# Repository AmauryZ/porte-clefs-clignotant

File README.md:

# Porte-clés clignotant 

## Contexte du projet 

Premier circuit imprimé réalisé à l'aide de Kicad consistant à faire clignoter alternativement deux LEDs (verte et bleue).

## Fonctionnement
Le circuit est composé d'un NE555 qui permet de faire clignoter alternativement les deux LEDs. La fréquence du cycle de clignotement est réglable via un potentiomètre.  
Le porte-clés est alimenté par deux piles boutons CR2032.

## Vidéos de démonstration du porte-clés réalisé

https://github.com/user-attachments/assets/a9404657-2942-4910-9b81-8aab252a95bd

https://github.com/user-attachments/assets/f14d513b-74e3-48db-ba6a-31ed8998a323

## Schématique \& PCB

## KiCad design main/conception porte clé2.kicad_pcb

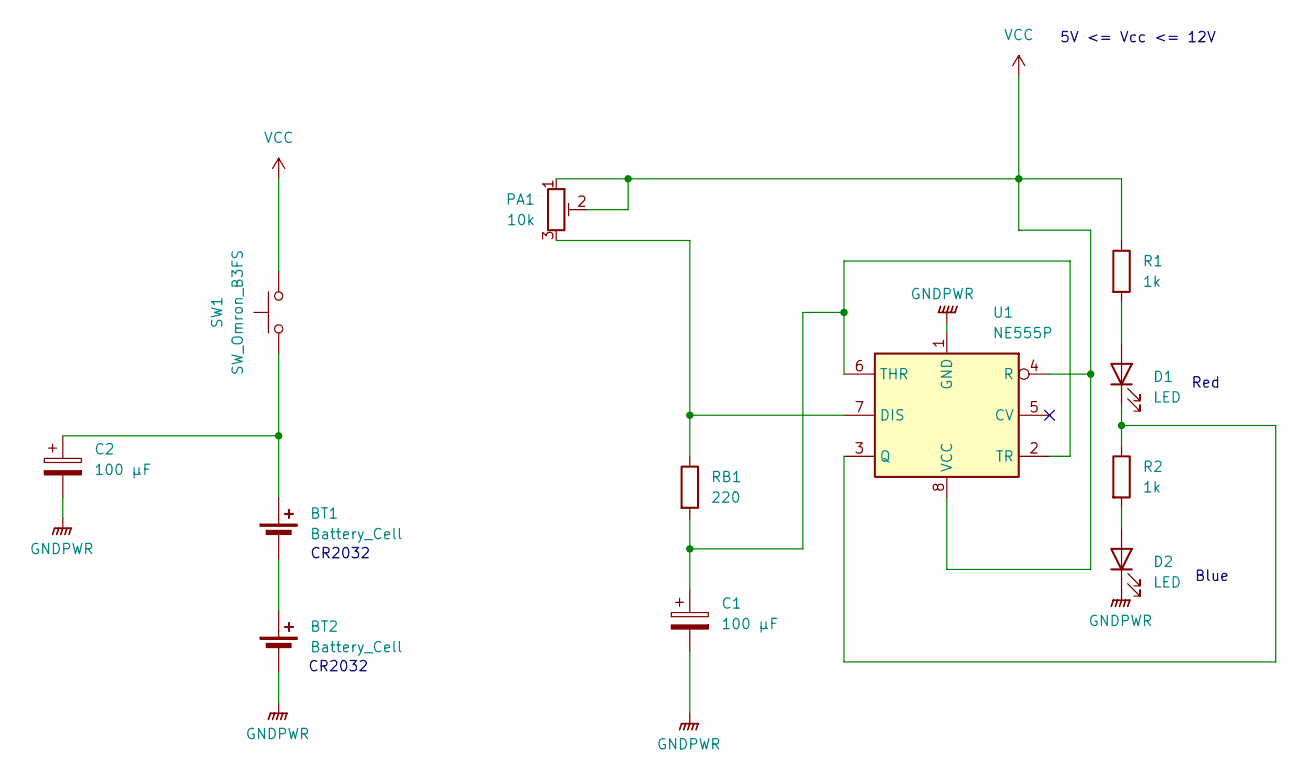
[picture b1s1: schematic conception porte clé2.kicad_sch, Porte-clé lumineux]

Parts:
BT1, BT2: Battery_Cell; BatteryHolder_MYOUNG_BS-07-A1BJ001_CR2032
C1, C2: 100 µF; CP_Radial_D12.5mm_P5.00mm
D1, D2: LED; LED_D5.0mm_Horizontal_O1.27mm_Z3.0mm
PA1: 10k; Potentiometer_Bourns_3266W_Vertical
R1, R2: 1k; R_Axial_DIN0207_L6.3mm_D2.5mm_P10.16mm_Horizontal
RB1: 220; R_Axial_DIN0207_L6.3mm_D2.5mm_P10.16mm_Horizontal
SW1: SW_Omron_B3FS; SW_SPST_Omron_B3FS-100xP
U1: NE555P; DIP-8_W7.62mm

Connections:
GNDPWR: BT2.2 (-), C1.2, C2.2, D2.1 (K), U1.1 (GND)
unnamed: BT1.1 (+), C2.1, SW1.1
unnamed: BT1.2 (-), BT2.1 (+)
unnamed: D1.2 (A), R1.2
unnamed: D1.1 (K), R2.1, U1.3 (Q)
unnamed: D2.2 (A), R2.2
unnamed: PA1.3, RB1.1, U1.7 (DIS)
unnamed: C1.1, RB1.2, U1.2 (TR), U1.6 (THR)
VCC: PA1.1, PA1.2, R1.1, SW1.2, U1.4 (R), U1.8 (VCC)

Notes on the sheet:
CR2032
5V <= Vcc <= 12V
Red
Blue

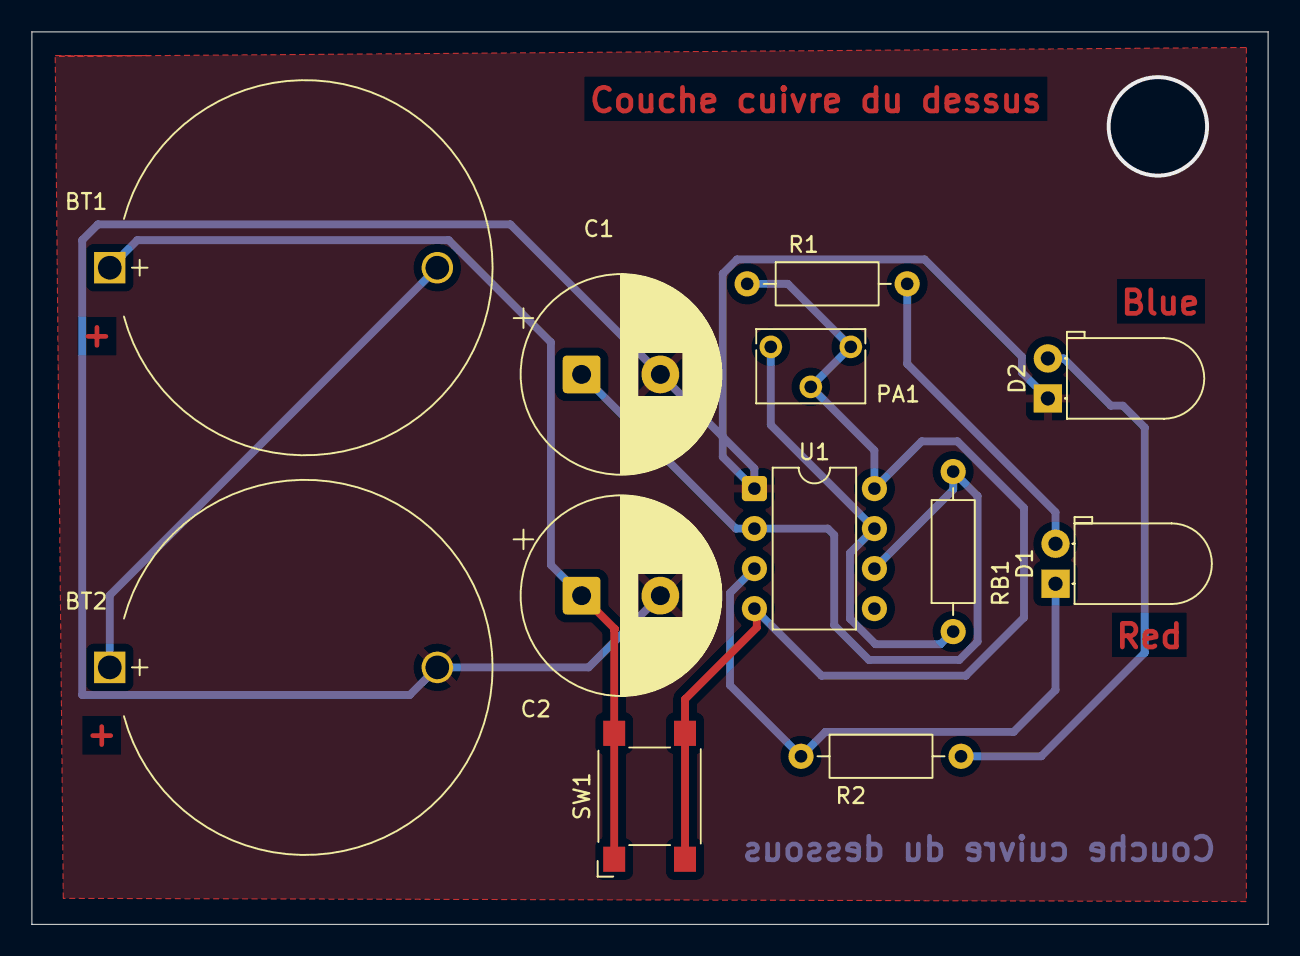
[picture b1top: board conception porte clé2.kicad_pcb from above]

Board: 2 copper layers, 78.5 x 56.7 mm, 12 parts (0 on the bottom side), 9 nets.
